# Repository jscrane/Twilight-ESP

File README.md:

View this project on [CADLAB.io](https://cadlab.io/project/1212).

# Twilight
Twilight for ESP. A new spin on an old idea.

See [blog articles](https://programmablehardware.blogspot.ie/search?q=twilight).

## Requires:
- Arduino 1.8.9
- ESP8266 [Arduino core](https://github.com/esp8266/Arduino) 3.0.1
- Wemos [D1 Mini](https://wiki.wemos.cc/products:d1:d1_mini)
- [PubSubClient](https://pubsubclient.knolleary.net) 2.8
- [ArduinoJson](https://github.com/bblanchon/ArduinoJson) 6.18.0
- [SimpleTimer](https://github.com/schinken/SimpleTimer)

## Features:
- Web [configuration](https://github.com/jscrane/WebConfiguredESP)
- [Domoticz](https://domoticz.com) integration via MQTT

## Circuit Diagram

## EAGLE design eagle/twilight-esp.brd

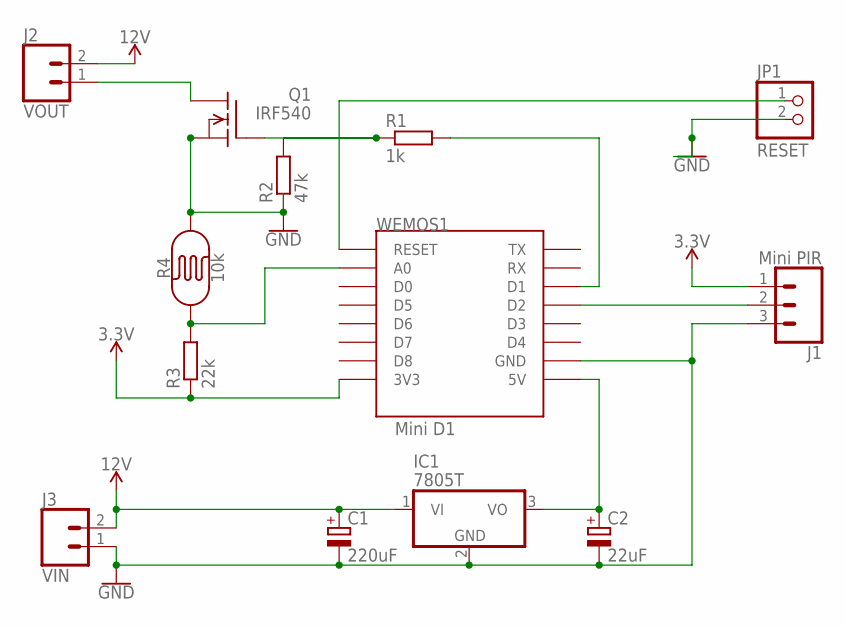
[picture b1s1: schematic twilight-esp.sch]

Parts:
C1: 220uF; E2-5
C2: 22uF; E2-4
IC1: 7805T; TO220H
J1: Mini PIR; 1X03
J2: VOUT; SCREWTERMINAL-5MM-2
J3: VIN; SCREWTERMINAL-5MM-2
JP1: RESET; 1X02
Q1: IRF540; TO220
R1: 1k; 0207/7
R2: 47k; 0207/7
R3: 22k; 0207/7
R4: 10k; PHOTOCELL
WEMOS1: Mini D1; WEMOS-D1-MINI

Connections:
3.3V: J1.1, R3.1, WEMOS1.3V3
12V: C1.+, IC1.1 (VI), J2.2, J3.2
GND: C1.-, C2.-, IC1.2 (GND), J1.3, J3.1, JP1.2, Q1.3 (S), R2.1, R4.2, WEMOS1.GND
unnamed: R1.2, WEMOS1.D1
unnamed: Q1.1 (G), R1.1, R2.2
unnamed: R3.2, R4.1, WEMOS1.A0
unnamed: JP1.1, WEMOS1.RESET
unnamed: J2.1, Q1.2 (D)
unnamed: J1.2, WEMOS1.D2
unnamed: C2.+, IC1.3 (VO), WEMOS1.5V

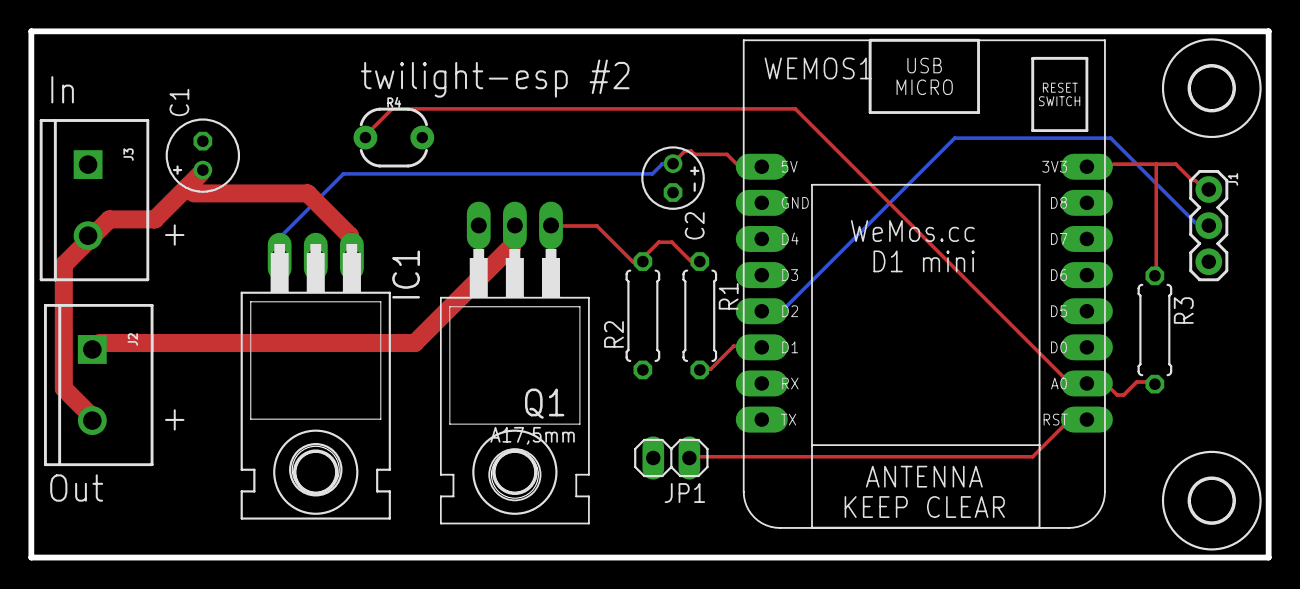
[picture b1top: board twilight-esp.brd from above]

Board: 2 copper layers, 87.0 x 37.0 mm, 17 parts (0 on the bottom side), 10 nets.

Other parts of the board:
U$1, U$2: 2,8
U$3, U$4: 3,0

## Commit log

2017-10-16 initial
2017-10-17 domoticz support
2017-10-17 eagle
2017-10-17 schematic
2017-10-22 add led
2017-11-19 JSON config, etc.
2017-11-19 reset after config update
2017-11-19 update schematic
2018-02-17 Cleanups
2018-02-18 bugfixes
2018-02-19 pwm and other cleanups
2018-02-20 config on/off_delay
2018-02-20 support mdns when not connected
2018-02-20 enable from domoticz
2018-02-20 updated schematic
2018-02-21 Monitor PIR during fade-out
2018-02-22 add gerbers
2018-02-22 explicit state machine
2018-02-22 remove debugging
2018-02-23 power led actually on D1
2018-02-24 cleanup
2018-02-24 add new states
2018-02-24 on and off brightness
2018-02-24 remove cruft; notify state on /power
2018-02-25 cleanup and bugfix
2018-02-25 strlcpy
2018-02-28 Create LICENSE
2018-03-10 add start state; flash pir led
2018-03-13 Use attachInterrupt for PIR. Remove delay() in loop(). Many cleanups.
2018-06-28 set autoreconnect. continue work as a light if disconnected from wifi(!)
2018-07-05 add reset header
2018-07-05 Backlink to CADLAB.io has been added.
2018-09-07 v2 gerbers
2018-11-03 update versions
2018-11-16 captive portal
2019-06-13 fix #9
2019-11-17 update deps
2019-11-17 configure PubSubClient
2019-11-19 define in Makefile
2019-12-09 fix #11
2019-12-20 timers
2019-12-20 minor updates
2019-12-26 increase domoticz json buffer size + bugfix
2020-01-04 add DOMOTICZ_CONTROL compile-time config
2020-01-11 add help info on config page, add configs for domoticz topics
2020-01-11 ignore spiffs.img
2020-01-17 fix #13
2020-01-24 fix #12
2020-04-19 debugging over mqtt
2020-04-29 - workaround case when stops turning off - update ArduinoJSON - more strings in flash - debugging to separate subtopics (mem/restart/state) - debugging messages are retained
2020-04-30 build subtopics as required; add debugger timer
2020-04-30 add uptime
2020-04-30 bugfix
2020-05-01 update hints
2020-05-01 move config into Configuration; rename topics
2020-05-02 version
2020-05-03 minor changes
2020-05-04 build with v2.7.0; add mqtt topics rssi and wifi
2021-02-02 update deps + announce core version over mqtt
2021-08-24 if switching on, don't announce pir beforehand
2021-09-15 revert bool->int pir
2021-09-16 prebuild step to copy config.skel to data/config.json if necessary
2021-10-05 remove domoticz-subscript option
2022-04-05 don't sleep wifi
2023-07-28 Makefile tweaks

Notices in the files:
eagle/twilight-esp.brd:
(c) 2018 steve
parts and their libraries:
SparkFun-Connectors: Licensing: Creative Commons ShareAlike 4.0 International - https://creativecommons.org/licenses/by-sa/4.0
